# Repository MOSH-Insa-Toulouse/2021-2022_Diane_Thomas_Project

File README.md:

# 2021-2022_Diane_Thomas_Project
Protocol de réalisation de capteurs low-tech à base de graphite

## Sommaire
 
  - [Test circuit avec LT-Spice](#test-circuit-avec-lt-spice)
  - [Réalisation PCB KICAD](#réalisation-pcb-kicad)
  - [Réalisation PCB physique](#réalisation-pcb-physique)
  - [Code Arduino](#code-arduino)
  - [APK MIT AppInventor](#apk-mit-appinventor)
  - [Banc de test](#banc-de-test)
  - [Amélioration à apporter](#amélioration-à-apporter)
  - [Point d'amélioration](#point-damélioration)
  - [Auteurs](#auteurs)

### Test circuit avec LT-Spice

Nous avons commencé par réaliser le circuit trans-impédance ci-dessus sur LT-Spice afin de déterminer la fonction de chaque filtre sur le circuit et aussi déterminer l'atténuation globale d'un bruit en courant de 50 Hz et aussi l'atténuation globale d'un bruit en courant à la fréquence limite de repliement.

1.1. Etude des filtres

Pour chaque filtre nous avons mesuré la fréquence de coupure expérimentalement avec LT-Spise et ensuite nous avons fait le calcul théorique avec la formule *fc=1/2*pi*R*C. Nous avons obtenus des valeurs expérimentales et théoriques très proches pour chaque filtre.

- Visualisation mesure filtre *R1C1*

Fréquence de coupure mesurée d'environ *16Hz*, ce filtre sert à filtrer le bruit de courant et aussi d'éviter les bruits de hautes fréquences causés par distorsion dans les étages d'entrée 

- Visualisation mesures filtre *R3C4*

Fréquence de coupure d'environ 1.6Hz, c'est un filtre actif passe bas qui permet d'avoir le maximum d'efficacité en maintenant le  gain constant.

- Visualition filtre R6C2

 Fréquence de coupure d'environ 1.6kHz, c'est le filtre de sortie qui permet d'adapter la fréquence du signal à la carte ADC arduino. Il empêche les fréquences élevées (bruit d'alimentation...) de passer dans l'ADC
 
 - La capacité C3 elle permet de filtrer le bruit d'alimentation.
 
 1.2. Etude de l'atténuation à la fréquence de coupure et à la fréquence de niquyst
 Gain global obtenu ~140dB
 - Atténuation à la fréquence de 50Hz
 
 A 50Hz on mesure un gain ~100dB ce qui traduit une atténution de ~ 40dB
 
 - Atténuation à la fréquence de niquyst=7.5kH
 
 A fniquyst on a un gain de 32.8dB, ce qui traduit une atténuation de ~ 100dB

## Réalisation PCB KICAD

Pour la réalisation de notre PCB nous avons utilisé le logiciel KICAD. Nous avons d'abord effectué le schématique en assignant à chaque composants (Bluetooth, oled, encodeur rotatoire) une empreinte et un symbole que nous avons réalisé, ensuite nous avons assigné à chaque composant un motif 3D pour la visualisation, et enfin nous avons effectué le routage de notre carte PCB

2.1. Schématique

2.2. Symbole et Empreinte des composants

-Module bluetooth

-Encodeur rotatoire

-Oled

2.3 Carte PCB 

2.4 Carte PCB visu 3d

## Réalisation PCB physique
Nous avons imprimé notre circuit sur une carte d'epoxy recouverte de cuivre qui est elle-même couverte par une résine positive photosensible.
Notre circuit a d'abord été imprimé(avec une imprimante classique à l'encre) sur du papier plastique transparent, faisant office de masque lors de l'insolation. 
Les motifs ont été ensuite transferrés sur la carte par insolation aux UV et un passage au développeur pour dissoudre la résine insolée.
Ensuite nous passons la carte dans un bain de perclorure de fer pour dissoudre les parties métalliques qui ont été revélées lors de l'insolation. 
Après cette étape, nous rinçons notre carte à l'eau et la plongeons dans un bain d'acétone pour enlever la résine qui protégeait les autres parties du circuit. 
Enfin l'on rince encore à l'eau et voilà, notre carte est prête. 
On utilise un foret pour le perçage et enfin on soude les composants(résistances, capacités, amplificateur,..... ) sur la carte.

## Code Arduino 
Dans notre code arduino, nous récuperons la valeur de la tension de notre capteur que nous convertissons en résistance. Nous affichons cette tension et cette  résistance sur l'oled et sur l'application que nous avons réalisée sur MIT AppIventor en envoyant la donnée de tension par le module Bluetooth. Une pression sur l'encodeur rotatoire permet de de changer l'affichage sur l'écran OLED, et de passer de l'affichage de la résistance à l'affichage de la tension (et inversement). 

Vous trouverez le code ici [Code arduino](https://github.com/MOSH-Insa-Toulouse/2021-2022_Diane_Thomas_Project/tree/main/Code_Biblioth%C3%A8que%20Arduino/code_capteur) .

## APK MIT AppInventor
Pour Installer l'application, il vous suffit de télécharger le fichier .apk sur votre téléphone et de l'installer.
Vous trouverez ce fichier dans ce dosssier [APK app inventor](https://github.com/MOSH-Insa-Toulouse/2021-2022_Diane_Thomas_Project/tree/main/APK%20app%20inventor).
L'application permet de lire les valeurs de résistance et de tension mesurées, et aussi de voir la courbe de mesure de la résistance.
Un bouton vous permet de vous connecter et vous déconnecter. Après la mesure il est possible de récuperer les valeurs de tension et de résistance mesurées dans un fichier txt qui s'enregistre automatiquement dans vos documents.

## Banc de test

Nous avons effectué notre banc de test en utilisant des cylindres de différents diamètres(1, 1.5, 2, 2.5, 3, 3.5, 4 cm) fabriqués avec du papier recyclé. On met le capteur en tension, en le faisant épouser la forme des différents cylindre).
Les resultats peuvent être consulté ici [Datasheet et banc de test](https://github.com/MOSH-Insa-Toulouse/2021-2022_Diane_Thomas_Project/tree/main/Datasheet%20et%20banc%20de%20test) .

## Amélioration à apporter
Notre banc de test présente certaines limites et peut être amélioré.
On a:

- La non répétabilité des mesures. En effet, les déformations appliquées peuvent varier entre chaque mesure: le banc de test ne permet pas d’appliquer une déformation identique. On pourrait envisager un banc de test fonctionnant avec un servomoteur par exemple (Ce système permet de générer des contraintes avec des angles bien précis et d'obtenir, de ce fait, une meilleure reproductibilité)

- Le dépôt de graphite sur le papier qui ne peut pas être maitrisé cela conduit une variation de mesure pour différents dépôts de même graphite.

-la déformation irréversible du capteur après un certains nombres de mesures.

#### Point d'amélioration

Afin de pouvoir lire une plus grande plage de résistance tout en ayant des mesures stables, il faudrait pouvoir changer le gain du circuit trans-impédance c'est à dire modifier la résistance R2 (voir schéma KiCad ). Cependant nous l'avons soudée sur le circuit PCB. Il faut donc à la place de la résistance R2 mettre un potentiomètre qui permet de varier  celle-ci.

## Auteurs
  
  - Bonkoungou Diane bonkoung@etud.insa-toulouse.fr
  - Bousquet Thomas tbousque@etud.insa-toulouse.fr

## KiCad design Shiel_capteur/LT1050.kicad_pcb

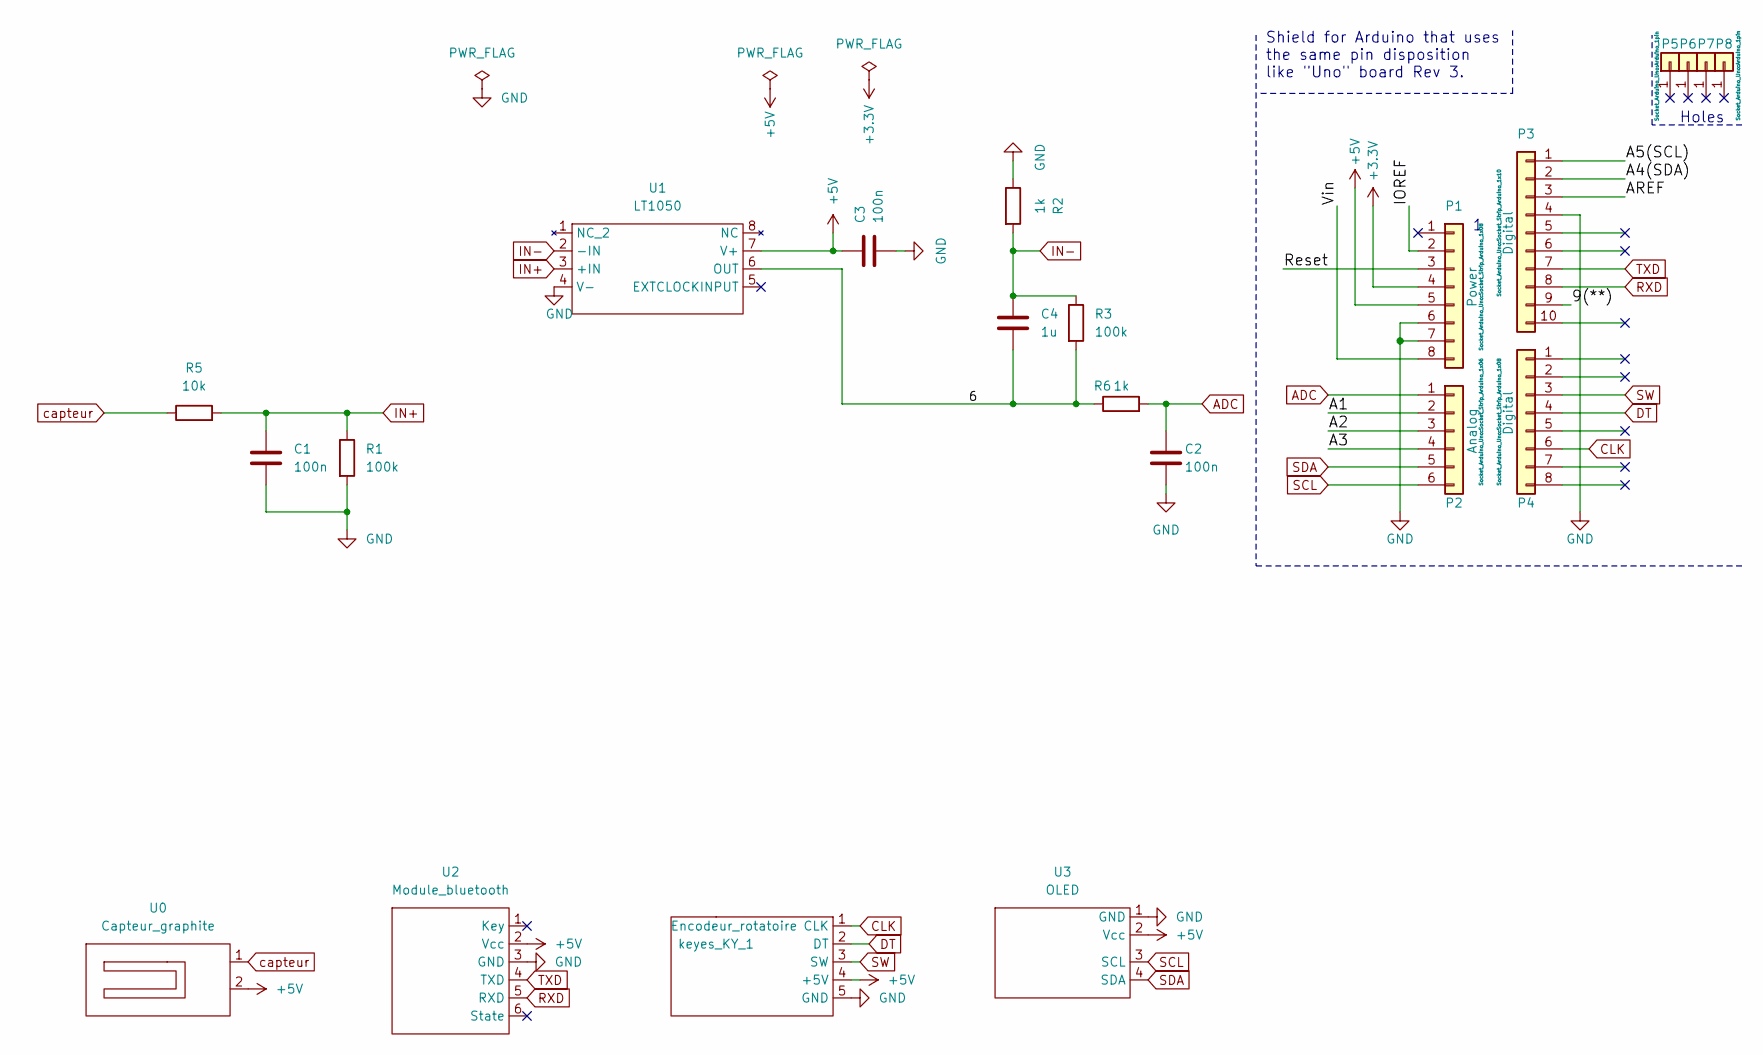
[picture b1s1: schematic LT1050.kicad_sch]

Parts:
C1, C2, C3: 100n; C_Disc_D3.4mm_W2.1mm_P2.50mm
C4: 1u; C_Rect_L7.5mm_W6.5mm_P5.00mm
P1: Power; Socket_Strip_Arduino_1x08
P2: Analog; Socket_Strip_Arduino_1x06
P3: Digital; Socket_Strip_Arduino_1x10
P4: Digital; Socket_Strip_Arduino_1x08
P5, P6, P7, P8: CONN_01X01; Arduino_1pin
R1, R3: 100k; R_Axial_DIN0207_L6.3mm_D2.5mm_P10.16mm_Horizontal
R2, R6: 1k; R_Axial_DIN0207_L6.3mm_D2.5mm_P10.16mm_Horizontal
R5: 10k; R_Axial_DIN0207_L6.3mm_D2.5mm_P10.16mm_Horizontal
U0: Capteur_graphite
U1: LT1050; DIP-8_296_ELL
U2: Module_bluetooth; Module bluetooth
U3: OLED
keyes_KY_1: Encodeur_rotatoire

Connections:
+3V3: P1.4
+5V: C3.1, P1.5, U0.2, U1.7 (V+), U2.2 (Vcc), U3.2 (Vcc), keyes_KY_1.4 (+5V)
/6: C4.2, R3.2, R6.1, U1.6 (OUT)
/9(**): P3.9
/A1: P2.2
/A2: P2.3
/A3: P2.4
/A4(SDA): P3.2
/A5(SCL): P3.1
/AREF: P3.3
/IOREF: P1.2
/Reset: P1.3
/Vin: P1.8
ADC: C2.1, P2.1, R6.2
CLK: P4.6, keyes_KY_1.1 (CLK)
DT: P4.4, keyes_KY_1.2 (DT)
GND: C1.2, C2.2, C3.2, P1.6, P1.7, P3.4, R1.2, R2.1, U1.4 (V-), U2.3 (GND), U3.1 (GND), keyes_KY_1.5 (GND)
IN+: C1.1, R1.1, R5.2, U1.3 (+IN)
IN-: C4.1, R2.2, R3.1, U1.2 (-IN)
RXD: P3.8, U2.5 (RXD)
SCL: P2.6, U3.3 (SCL)
SDA: P2.5, U3.4 (SDA)
SW: P4.3, keyes_KY_1.3 (SW)
TXD: P3.7, U2.4 (TXD)
capteur: R5.1, U0.1

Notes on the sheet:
Holes
Shield for Arduino that uses the same pin disposition like "Uno" board Rev 3.

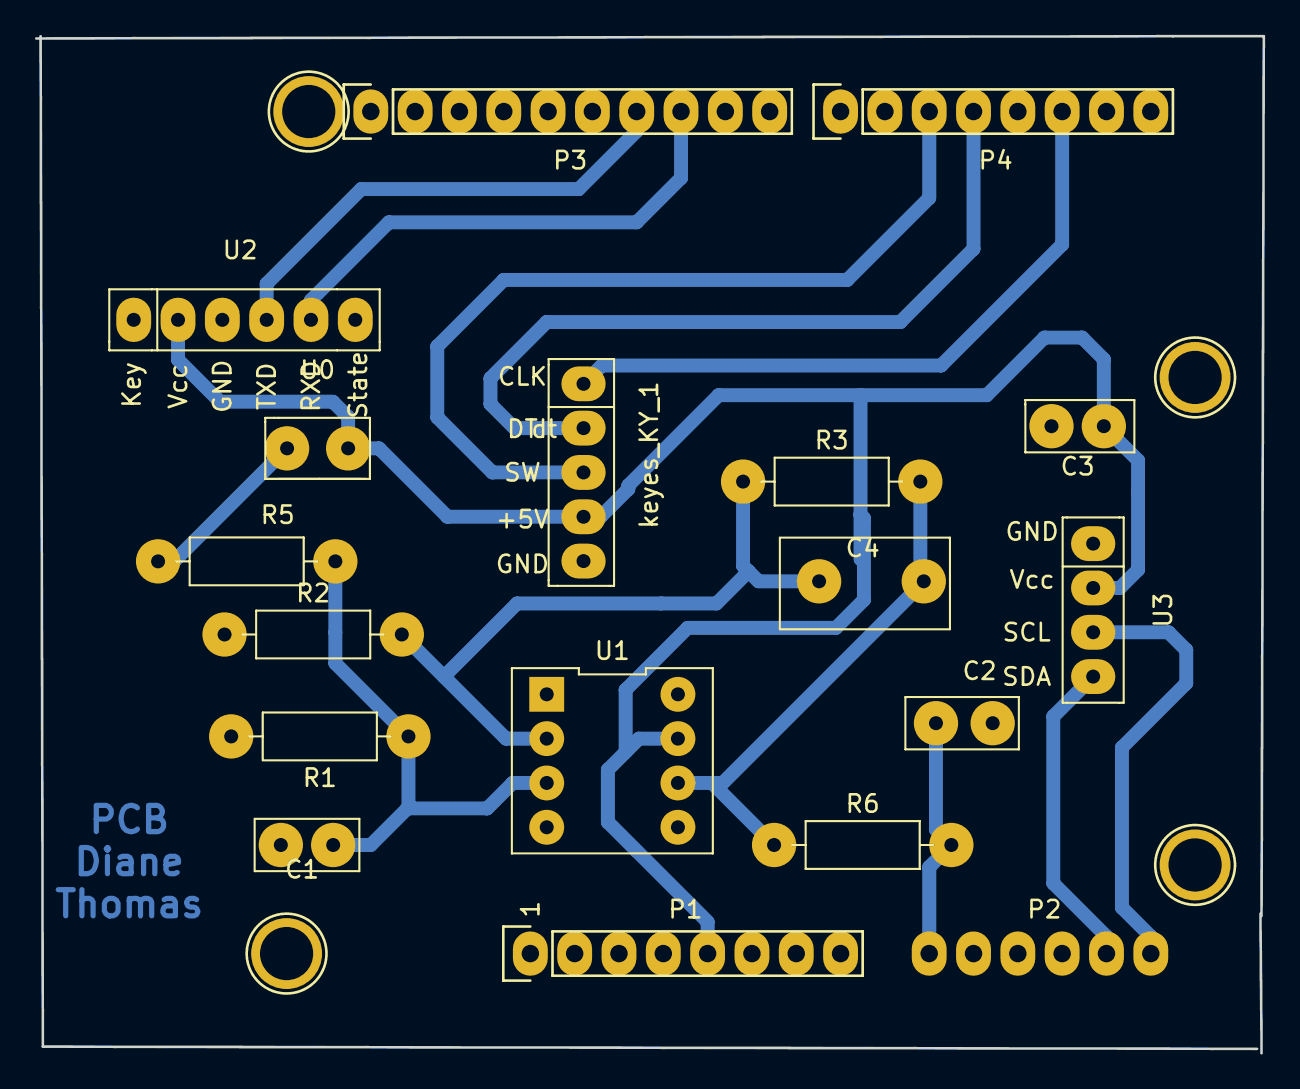
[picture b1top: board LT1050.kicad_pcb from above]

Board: 2 copper layers, 70.4 x 58.3 mm, 22 parts (0 on the bottom side), 14 nets.

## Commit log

2022-03-06 version initiale
2022-03-08 ajout kicad
2022-03-08 suppression kicad
2022-03-08 suppression
2022-03-08 suppressionu
2022-03-11 ajout de fichier kicad
2022-03-11 mis à jour kicad
2022-03-15 correction routage
2022-03-16 ajout tracerkicad
2022-03-16 mise à jour pcb
2022-03-30 correction cathy
2022-03-31 ajout ltspice
2022-03-31 mise à jour correction kicad Cathy
2022-03-31 ajout info ltspice
2022-04-01 kicad plan de masse
2022-04-04 ajout fichier Fsilcreen
2022-04-12 fin kicad et ajout ltspice
2022-04-12 ajout kicaglast
2022-04-15 nom kicad_change
2022-04-15 ajout code arduino
2022-04-15 ajout dossier datasheet
2022-04-18 modification code arduino
2022-04-18 ajout appinventor
2022-04-18 ajout datasheet
2022-04-18 ajout detail apk
2022-04-18 ajout pcb
2022-05-16 sensibility add
2022-05-16 ajout sensibilité capteur
2022-05-16 fautesssss
2022-05-16 corrections
